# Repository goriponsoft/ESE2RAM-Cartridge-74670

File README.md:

# 似非²RAMカートリッジ(1Mbyte版)
[English README is here](README-en.md)

これは、汎用ロジックICによりメガROMコントローラと同等の動作を実現し、それを利用して似非RAMを構築したMSX用カートリッジ(命名:似非・似非RAMまたは似非²RAM)です。
ごりぽんハードウェア(同人サークル・ごりぽんソフトウェアのハードウェア部門)により作成されました。

KiCAD7用の回路図データ・基板データ・ガーバーデータを、クリエイティブ・コモンズライセンス(CC-BY-NC)で公開しています。
[MGINST215.zip](https://github.com/goriponsoft/ESE2RAM-Cartridge-74670/blob/main/MGINST215.zip)および[KSAVER105.zip](https://github.com/goriponsoft/ESE2RAM-Cartridge-74670/blob/main/KSAVER105.zip)はCCライセンスの対象ではなく、元のライセンスと条件が適用されます。

X(旧Twitter): @goriponsoft

## 似非RAMディスク(似非RAM)とは？

[同人サークル・似非職人工房](http://www.hat.hi-ho.ne.jp/tujikawa/ese/)のつじかわ氏が考案した、ストレージなどとして使えるMSX用の汎用バックアップRAMカートリッジです。

通常は、ゲームのメガROMカートリッジを改造し、ROMをRAMに置き換えることで制作します。MGINSTコマンドによりDOSカーネルをインストールしてSSDのようなストレージとして利用したり(似非RAMディスク)、メガROMのイメージを読み込ませて動作させたりすることができます。

もともとストレージとしての使用を前提に考案されたため、カートリッジ自体も「似非RAMディスク」と呼ぶほうが一般的です。

なお、所有していないゲームのイメージを読み込ませて利用することは違法行為です。通常は似非RAMディスクの他、似非RAMに改造することで使用できなくなる改造元ゲームカートリッジのイメージ(改造前にファイルに書き出しておく必要あり)、フリーウェア、自作ROMゲーム、などを動作させるのに使用します。

似非RAMディスクについての詳細は、[似非職人工房の似非RAMディスクのページ](http://www.hat.hi-ho.ne.jp/tujikawa/ese/eseram.html)を参照してください。

## 似非²RAM(似非・似非RAM)とは？

近年MSXゲームの入手自体が難しくなり、貴重になってしまったメガROMカートリッジを潰して似非RAMにするのはかなり躊躇われる状況でした。そこで、普通に入手できる汎用ロジックICを使い、メガROMコントローラーと同等の回路を実現し、それを利用して似非RAMとして組み上げたのがこのカートリッジです。

似非RAMでありながら、メガROMコントローラを使用していない「似て非なる似非RAM」ということで「似非・似非RAM」、転じて「似非の2乗」で「似非²RAM」と命名しました。上付き文字の使用に問題がある場合は「似非2RAM」や「似非似非RAM」でも構いません。英語表記は「ESE-ESE-RAM」または「ESE2-RAM」です。

## 部品表
注意: 基板Rev.6以降U3～U5が74HCシリーズから74AHCシリーズに変更されています
|部品番号|内容|数量|
|:--|:--|--:|
|BT1|CR2032電池ホルダ "CH29-2032LF"/"CH28-2032LF(TR)"/"CH004-2032LF"/"CH004-2032LF"のいずれか|1|
|C1-C8|セラミックコンデンサ 0.1μF・50V・2.5mmピッチ|8|
|C9|電解コンデンサ 47μF・16V|1|
|D1-D2|ダイオード "1N4148"|2|
|IC1-IC2|4Mbit SRAM(628512タイプ・512K×8) DIP-32 "AS6C4008"など|2|
|R1-R4|抵抗 1/4W・10KΩ|4|
|RN1|集合抵抗 8素子・10KΩ SIP-9|1|
|S1|6×6mm タクトスイッチ "TVDP01-095BB1"|1|
|U1-U2|汎用ロジックIC "74HC670"|2|
|U3|汎用ロジックIC "74AHC138"|1|
|U4|汎用ロジックIC "74AHC00"|1|
|U5|汎用ロジックIC "74AHC32"|1|
|-|CR2032電池|1|

## 組み立て方
基板の実装面積の関係で、抵抗、コンデンサ、ダイオードなどの部品が裏面(ハンダ面)に配置されているため、組み立てには注意が必要です。

[詳細な組み立てマニュアル(日本語版)はこちら](assemble_manual/main.md)

1. 基板を裏返して(コネクタの傍に「Front」と書かれている側が表面です)、シルク印刷を参考に、ダイオード、抵抗、セラミックコンデンサ、集合抵抗、の順で部品を配置して表側(部品面)からハンダ付けします。ハンダを盛りすぎると、ICと基板の間に隙間ができるので、ハンダの量は控えめにしてハンダ付けしてください。
2. ハンダ付けしたら、表面に余ったリードを切断します。リードが余分に残っていると、やはりICと基板の間に隙間ができるので、こちらもできるだけ短くなるように切断してください。
3. 基板を表に戻し、IC、電解コンデンサ、セラミックコンデンサを配置し、通常通り裏面(ハンダ面)からハンダ付けしていきます。電解コンデンサはシルク印刷の方向に横倒しにして実装してください(縦に実装するとカートリッジシェルに収まりません)。ICやコンデンサのリードの処理は通常通りで構いません。
4. タクトスイッチと電池ホルダをハンダ付けします。標準では、タクトスイッチは裏面、電池ホルダは表面に配置しますが、逆の面に配置することもできますので、お好みで配置してください。
5. ショートや部品の付け間違いがないことを念入りに確認したうえで、MSX実機に挿して動作を確認します。似非RAMディスクとして使わない場合でも、動作確認にはMGINSTを使うのが簡単です。

## 準備 (似非RAMディスクとして使う場合)
1. 似非インストーラー(MGINST.COM)とカーネルセーバー(KSAVER.COM)を入手します([似非職人工房・非公認出張所(似非なページ)](http://www.big.or.jp/~saibara/msx/ese/index-j.html)よりLHA形式のアーカイブをダウンロードすることができます。また、ZIP形式にアーカイブしなおした[MGINST215.zip](https://github.com/goriponsoft/ESE2RAM-Cartridge-74670/blob/main/MGINST215.zip)と[KSAVER105.zip](https://github.com/goriponsoft/ESE2RAM-Cartridge-74670/blob/main/KSAVER105.zip)も、こちらで用意してあります。)
2. 何らかのMSXで起動可能なストレージ(通常はフロッピーディスク)に上記ツールを展開したものと、MSX-DOSのシステムファイル(MSXDOS.SYS/COMMAND.COM)をコピーします。MSX-DOS2カーネル利用の場合は、加えてMSX-DOS2のシステムファイル(MSXDOS2.SYS/COMMAND2.COM)をコピーしておくと、似非RAMインストール時に自動的にコピーされ、MSX-DOS2で起動することができるようになります。
3. MSX実機に似非²RAMカートリッジを挿し、タクトスイッチを押したまま電源を入れ、手順2で作成したストレージからMSX-DOS(またはMSX-DOS2)を起動します。
4. KSAVER.COMを使用し、MSX本体からMSX-DOSまたはMSX-DOS2のカーネルをファイルに保存します(詳細はKSAVERの付属ドキュメントを参照)。
5. MGINST.COMを使用し、手順4で保存したカーネルのファイルを指定して似非RAMカーネルをインストールします(詳細はMGINSTの付属ドキュメントを参照)。
6. リセットし似非RAMディスクから起動することを確認します。

手順4で保存したカーネルファイルは不要ですので、削除してしまっても構いません。残しておくと、似非RAMディスクの再インストール時に手順を省略できます。

手順5でエラーが出る場合は、部品のハンダ付け不良の可能性が高いので、基板をチェックしてみてください。

## 使い方 (メガROMソフトウェアを動かす場合)
使用した部品の機能の関係で、当カートリッジでは、セグメント番号の初期値がASCIIマッパーと異なっているため、プログラムによるレジスタの初期化が必須となっています。似非RAMディスクやゲームを含む、ほとんどのメガROMソフトウェアでは適切に初期化が行われているので問題ありませんが、初期化を怠っていたり、セグメント初期値が特定の値であることを期待しているソフトウェアは動作しない場合があります。

当カートリッジの起動直後もしくはリセット直後のバンクは以下のようになっています。

|バンクアドレス|レジスタアドレス|セグメント番号|
|:--|:--|--:|
|4000h-5FFFh|6000h-67FFh|0|
|6000h-7FFFh|6800h-6FFFh|0|
|8000h-9FFFh|7000h-77FFh|0|
|A000h-BFFFh|7800h-7FFFh|0|

この状態からレジスタに値を書き込むと、書き込んだレジスタは書き込んだ値に、書き込まれていないレジスタは不定値に切り替わります。

例えば6000hに0を書き込んだ場合は以下のようになります。

|バンクアドレス|セグメント番号|
|:--|--:|
|4000h-5FFFh|0|
|6000h-7FFFh|不定|
|8000h-9FFFh|不定|
|A000h-BFFFh|不定|

このため、当カートリッジで自作メガROMソフトウェアを動作させる場合は、INITエントリのできるだけ早い段階で、実行中のアドレスを含むバンクのレジスタに0を書き込んで初期化する必要があります。実行中のアドレスを含まないバンクのレジスタに先に書き込んでしまうと、実行中のプログラムが不定のバンクに切り替わり、ほとんどの場合は暴走します。また、書き込まれなかったレジスタの値は不定ですので、必要であれば初期化を行ってください。

通常はセグメント#0に以下のコードを配置し、ROMヘッダのINITエントリより4000h～5FFFhバンクのコードとして呼び出せば、問題なく初期化できます。
```
	xor		a
	ld		(6000h),a
	ld		(6800h),a
	ld		(7000h),a
	ld		(7800h),a
```

## 互換性情報
動作確認済のハードウェア(順不同)について

ご報告いただいたものは順次追加していきます

### 動作不良が確認されている機種と症状

- ビクター HC-90 および HC-95 (MSX2) : RAMから読み出されたデータが壊れるため正常動作しない
- 東芝 HX-E601 (拡張スロット) : 認識されず起動しない

### 正常動作が確認されている機種

- パナソニック FS-A1ST
- ソニー HB-F1XV
- 三菱 ML-G30model1 および ML-G30model2
- ヤマハ YIS503 および CX5F
- ヤマハ YIS604/128 および CX7M/128
- 三洋 WAVY70FD および WAVY70FD2
- 東芝 HX-31
- 三菱 ML-8000
- ゼネラル PCT-50 および PCT-55
- ソニー HB-F500

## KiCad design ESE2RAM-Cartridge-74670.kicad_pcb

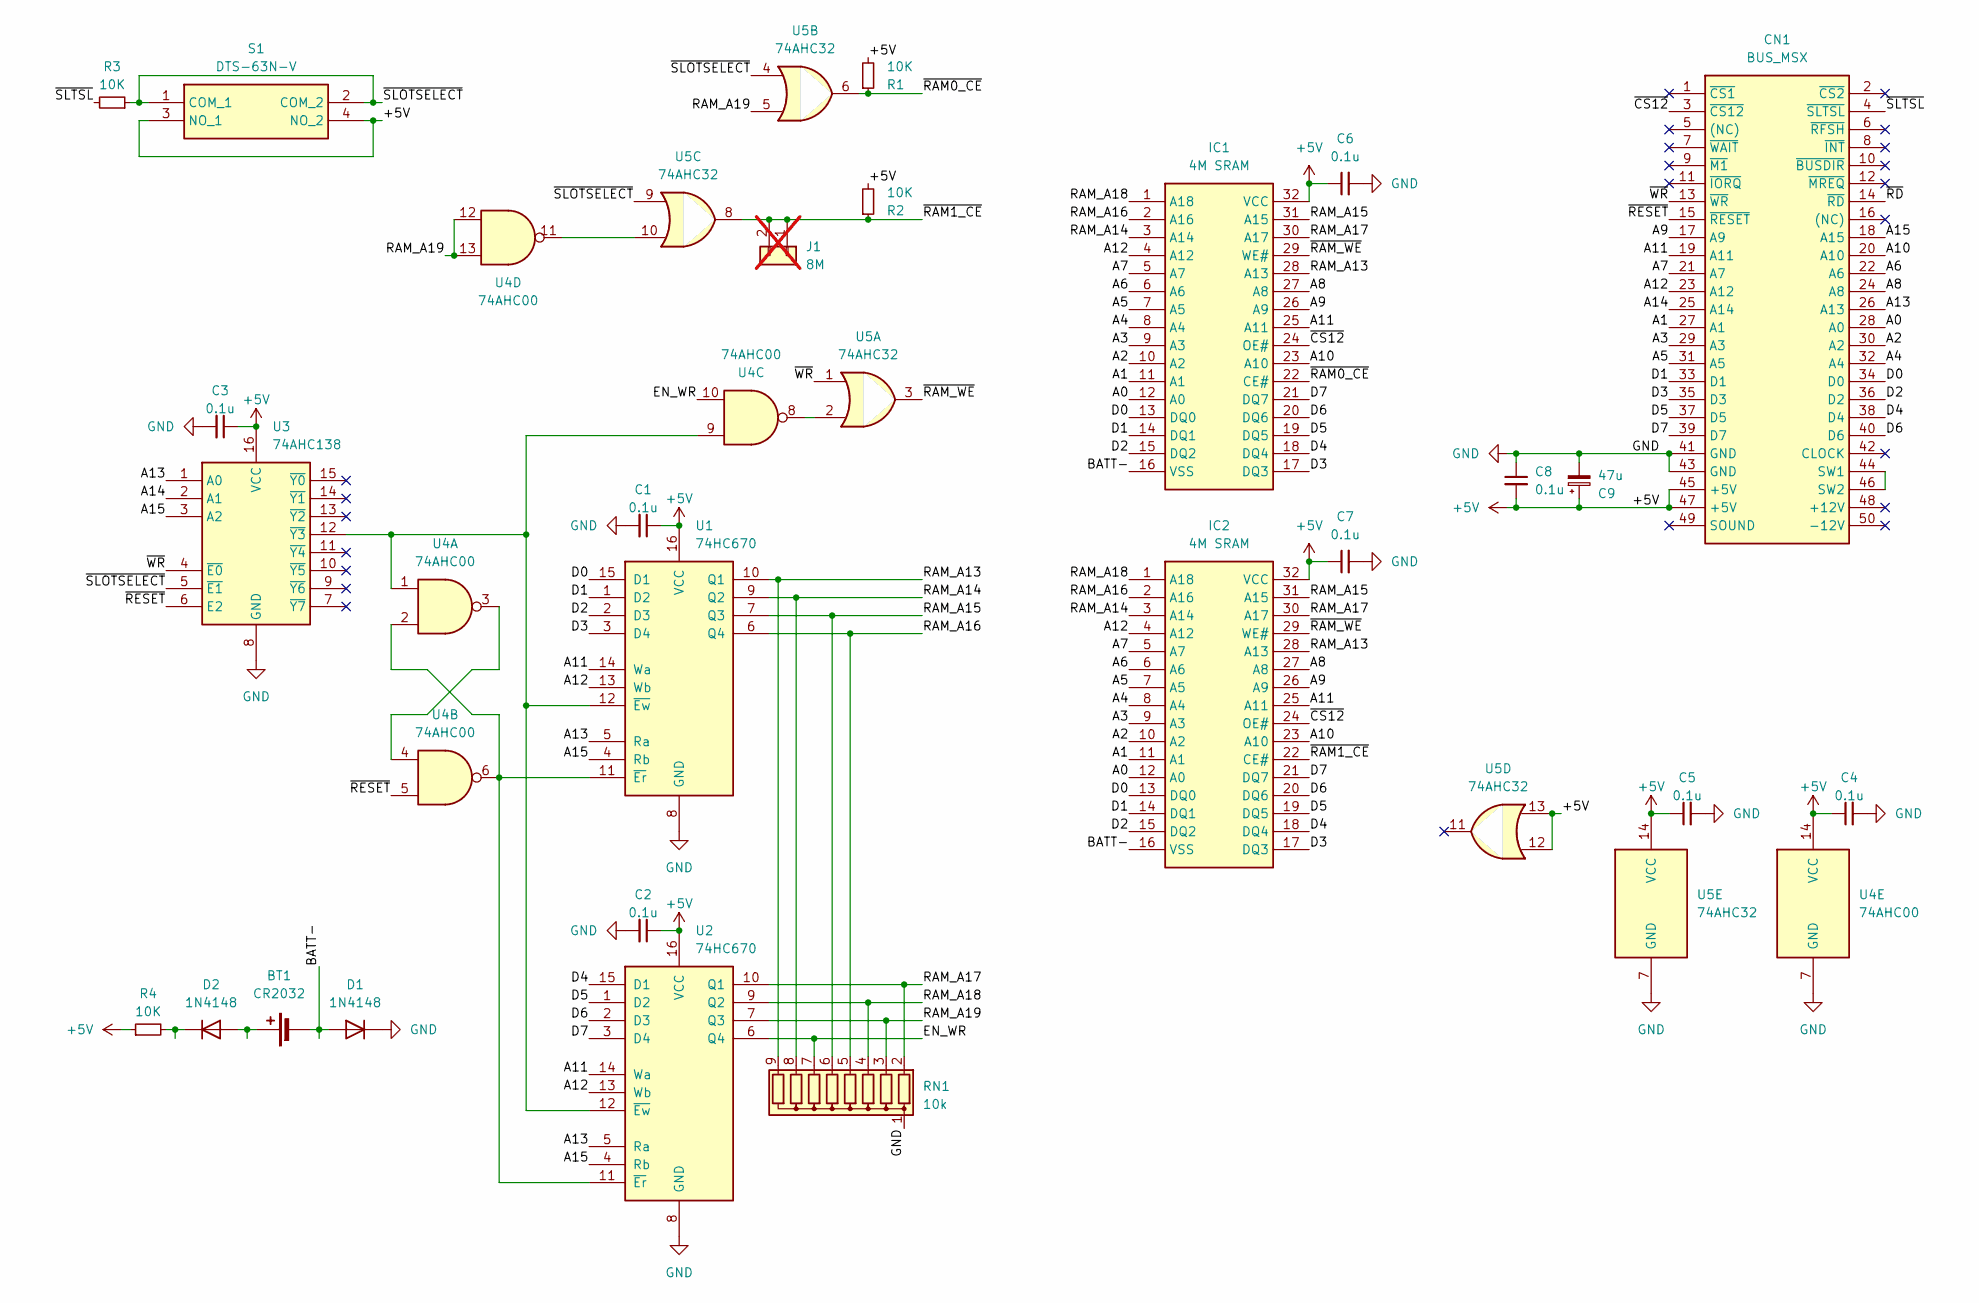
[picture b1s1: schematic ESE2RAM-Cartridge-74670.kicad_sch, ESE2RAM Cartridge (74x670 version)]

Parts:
BT1: CR2032; BatteryHolder_CH2x-2032LF
C1, C2, C3, C4, C5, C6, C7, C8: 0.1u; C_Disc_D3.0mm_W1.6mm_P2.50mm
C9: 47u; CP_Radial_D5.0mm_P2.00mm_Horizontal
CN1: BUS_MSX; BUS_MSX_CARD_SHORT
D1, D2: 1N4148; D_DO-35_SOD27_P7.62mm_Horizontal
IC1, IC2: 4M SRAM; DIP32_600mil_FineLongPad; Manufacturer_Part_Number AS6C4008-55PIN; Mouser Part Number 913-AS6C4008-55PIN
J1: 8M; PinHeader_1x02_P2.00mm_Vertical; not fitted
R1, R2, R3, R4: 10K; R_Axial_DIN0207_L6.3mm_D2.5mm_P7.62mm_Horizontal
RN1: 10k; R_Array_SIP9
S1: DTS-63N-V; DTS63NV; Manufacturer_Part_Number DTS-63N-V; Mouser Part Number 113-DTS-63N-V
U1, U2: 74HC670; DIP16_300mil_FineLongPad
U3: 74AHC138; DIP16_300mil_FineLongPad
U4: 74AHC00; DIP14_300mil_FineLongPad
U5: 74AHC32; DIP14_300mil_FineLongPad

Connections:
+5V: C1.1, C2.1, C3.1, C4.1, C5.1, C6.1, C7.1, C8.2, C9.1, CN1.45 (+5V), CN1.47 (+5V), IC1.32 (VCC), IC2.32 (VCC), R1.2, R2.2, R4.1, S1.3 (NO_1), S1.4 (NO_2), U1.16 (VCC), U2.16 (VCC), U3.16 (VCC), U4.14 (VCC), U5.12, U5.13, U5.14 (VCC)
/A0: CN1.28 (A0), IC1.12 (A0), IC2.12 (A0)
/A1: CN1.27 (A1), IC1.11 (A1), IC2.11 (A1)
/A2: CN1.30 (A2), IC1.10 (A2), IC2.10 (A2)
/A3: CN1.29 (A3), IC1.9 (A3), IC2.9 (A3)
/A4: CN1.32 (A4), IC1.8 (A4), IC2.8 (A4)
/A5: CN1.31 (A5), IC1.7 (A5), IC2.7 (A5)
/A6: CN1.22 (A6), IC1.6 (A6), IC2.6 (A6)
/A7: CN1.21 (A7), IC1.5 (A7), IC2.5 (A7)
/A8: CN1.24 (A8), IC1.27 (A8), IC2.27 (A8)
/A9: CN1.17 (A9), IC1.26 (A9), IC2.26 (A9)
/A10: CN1.20 (A10), IC1.23 (A10), IC2.23 (A10)
/A11: CN1.19 (A11), IC1.25 (A11), IC2.25 (A11), U1.14 (Wa), U2.14 (Wa)
/A12: CN1.23 (A12), IC1.4 (A12), IC2.4 (A12), U1.13 (Wb), U2.13 (Wb)
/A13: CN1.26 (A13), U1.5 (Ra), U2.5 (Ra), U3.1 (A0)
/A14: CN1.25 (A14), U3.2 (A1)
/A15: CN1.18 (A15), U1.4 (Rb), U2.4 (Rb), U3.3 (A2)
/BATT-: BT1.2 (-), D1.2 (A), IC1.16 (VSS), IC2.16 (VSS)
/D0: CN1.34 (D0), IC1.13 (DQ0), IC2.13 (DQ0), U1.15 (D1)
/D1: CN1.33 (D1), IC1.14 (DQ1), IC2.14 (DQ1), U1.1 (D2)
/D2: CN1.36 (D2), IC1.15 (DQ2), IC2.15 (DQ2), U1.2 (D3)
/D3: CN1.35 (D3), IC1.17 (DQ3), IC2.17 (DQ3), U1.3 (D4)
/D4: CN1.38 (D4), IC1.18 (DQ4), IC2.18 (DQ4), U2.15 (D1)
/D5: CN1.37 (D5), IC1.19 (DQ5), IC2.19 (DQ5), U2.1 (D2)
/D6: CN1.40 (D6), IC1.20 (DQ6), IC2.20 (DQ6), U2.2 (D3)
/D7: CN1.39 (D7), IC1.21 (DQ7), IC2.21 (DQ7), U2.3 (D4)
/EN_WR: RN1.7 (R6), U2.6 (Q4), U4.10
/RAM_A13: IC1.28 (A13), IC2.28 (A13), RN1.9 (R8), U1.10 (Q1)
/RAM_A14: IC1.3 (A14), IC2.3 (A14), RN1.8 (R7), U1.9 (Q2)
/RAM_A15: IC1.31 (A15), IC2.31 (A15), RN1.6 (R5), U1.7 (Q3)
/RAM_A16: IC1.2 (A16), IC2.2 (A16), RN1.5 (R4), U1.6 (Q4)
/RAM_A17: IC1.30 (A17), IC2.30 (A17), RN1.2 (R1), U2.10 (Q1)
/RAM_A18: IC1.1 (A18), IC2.1 (A18), RN1.4 (R3), U2.9 (Q2)
/RAM_A19: RN1.3 (R2), U2.7 (Q3), U4.12, U4.13, U5.5
/~CS12: CN1.3 (~CS12), IC1.24 (OE#), IC2.24 (OE#)
/~RAM0_CE: IC1.22 (CE#), R1.1, U5.6
/~RAM1_CE: IC2.22 (CE#), J1.1, J1.2, R2.1, U5.8
/~RAM_WE: IC1.29 (WE#), IC2.29 (WE#), U5.3
/~RD: CN1.14 (~RD)
/~RESET: CN1.15 (~RESET), U3.6 (E2), U4.5
/~SLOTSELECT: R3.1, S1.1 (COM_1), S1.2 (COM_2), U3.5 (~E1), U5.4, U5.9
/~SLTSL: CN1.4 (~SLTSL), R3.2
/~WR: CN1.13 (~WR), U3.4 (~E0), U5.1
GND: C1.2, C2.2, C3.2, C4.2, C5.2, C6.2, C7.2, C8.1, C9.2, CN1.41 (GND), CN1.43 (GND), D1.1 (K), RN1.1 (common), U1.8 (GND), U2.8 (GND), U3.8 (GND), U4.7 (GND), U5.7 (GND)
unnamed: BT1.1 (+), D2.2 (A)
unnamed: CN1.44 (SW1), CN1.46 (SW2)
unnamed: D2.1 (K), R4.2
unnamed: U1.11 (~Er), U2.11 (~Er), U4.2, U4.6
unnamed: U1.12 (~Ew), U2.12 (~Ew), U3.12 (~Y3), U4.1, U4.9
unnamed: U4.3, U4.4
unnamed: U4.8, U5.2
unnamed: U4.11, U5.10

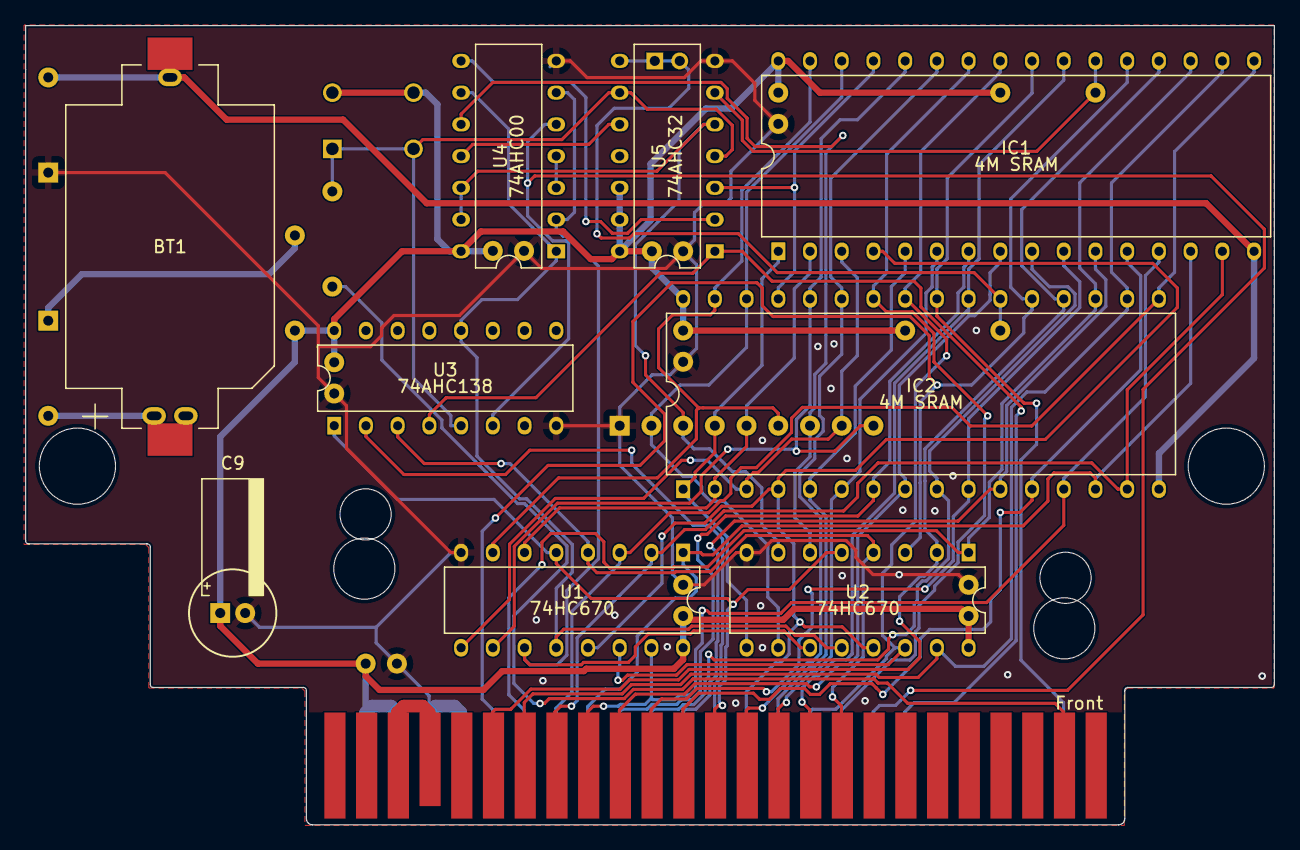
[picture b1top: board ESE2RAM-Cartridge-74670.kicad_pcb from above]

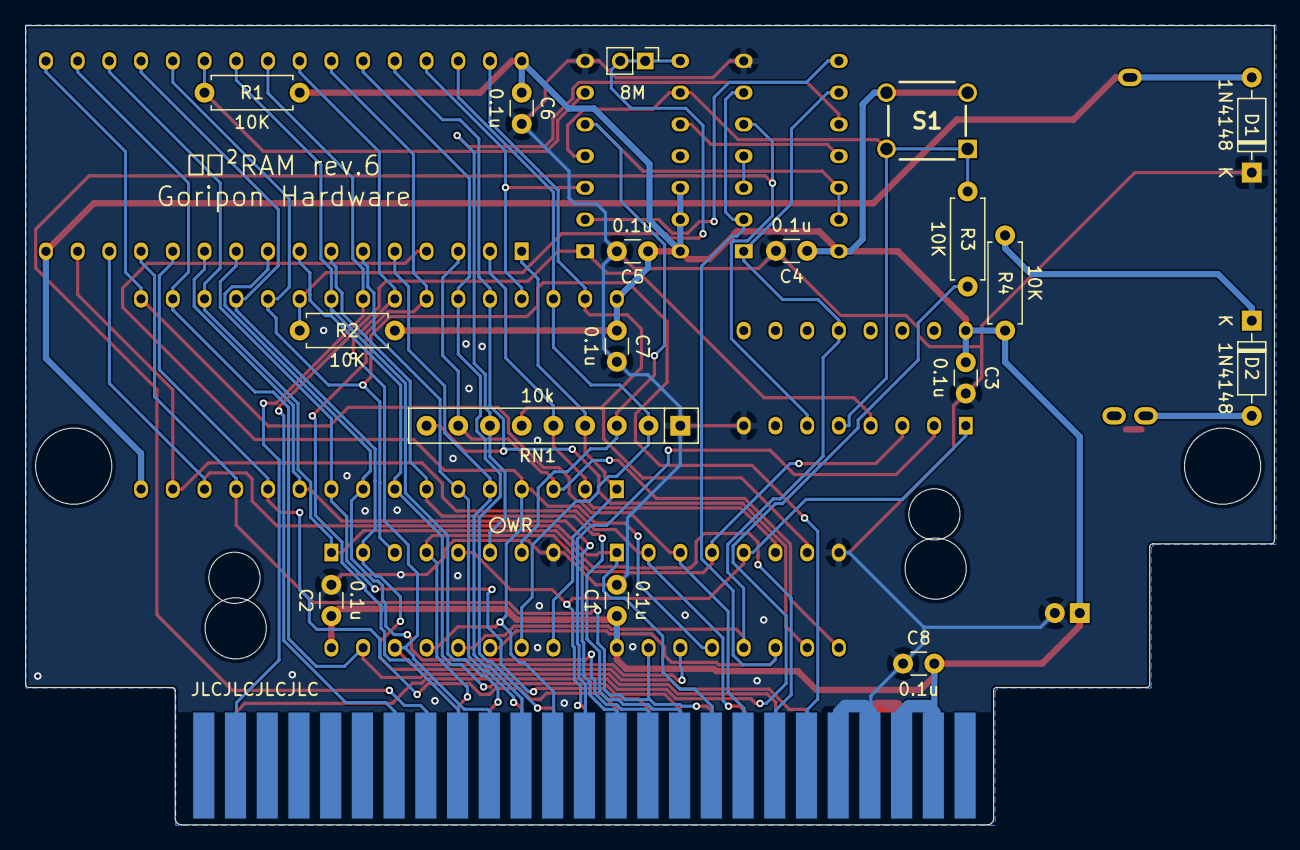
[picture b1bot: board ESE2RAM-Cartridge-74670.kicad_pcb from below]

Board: 2 copper layers, 100.0 x 64.0 mm, 27 parts (17 on the bottom side), 51 nets.

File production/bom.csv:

Designator,Footprint,Quantity,Value,LCSC Part #
BT1,BatteryHolder_CH2x-2032LF,1,CR2032,
"C1, C2, C3, C4, C5, C6, C7, C8",C_Disc_D3.0mm_W1.6mm_P2.50mm,8,0.1u,
C9,CP_Radial_D5.0mm_P2.00mm_Horizontal,1,47u,
"D1, D2",D_DO-35_SOD27_P7.62mm_Horizontal,2,1N4148,
"IC1, IC2",DIP32_600mil_FineLongPad,2,4M SRAM,
"R1, R2, R3, R4",R_Axial_DIN0207_L6.3mm_D2.5mm_P7.62mm_Horizontal,4,10K,
RN1,R_Array_SIP9,1,10k,
S1,DTS63NV,1,DTS-63N-V,
"U1, U2",DIP16_300mil_FineLongPad,2,74HC670,
U3,DIP16_300mil_FineLongPad,1,74AHC138,
U4,DIP14_300mil_FineLongPad,1,74AHC00,
U5,DIP14_300mil_FineLongPad,1,74AHC32,

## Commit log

2024-03-24 First Release
2024-03-25 Modified README
    Modified README
    Added "How to assemble" item.
2024-03-25 Modified schematic
    Modified schematic
    Change tactile switch.
2024-03-25 Modified README
    Modified README
    Corrected "Preparation" item.
2024-03-25 Modified Schematic
    Modified Schematic
    Fixed DRC error in PCB data & Rebuilt Gerber data.
2024-03-27 Modified README
    公開しているデータについての説明を追加。
    Added explanation about published data.
2024-03-28 Modified README
    部品表のセラミックコンデンサにリード間隔を追加、組み立て方に動作確認の手順を追加、ほか細かい文言の修正。
    Added lead spacing to ceramic capacitors in the parts list, added operation confirmation steps to assembly instructions, and other minor wording corrections.
2024-03-31 Added tools archive.
    ツール類のzipアーカイブを追加。
    Added tool zip archive.
2024-03-31 Modified README
    KSAVER105.zipのライセンスに関する項目が抜けていたので追加。
    Added the item related to the license of KSAVER105.zip because it was missing.
2024-04-04 Modify Schematic
    プロジェクトローカルライブラリの設定が抜けていたのを修正。
    Fixed missing project local library settings.
    その他の細かな修正。
    Other minor corrections.
2024-04-12 Modified Schematic
    電解コンデンサの容量を10μFから47μFに変更
    電池ソケットのシルク印刷の切り欠き位置が間違っていたのを修正
    不要なファイルの削除
    その他細かな修正
    Changed the capacitance of electrolytic capacitor from 10uF to 47uF.
    Fixed an issue where the notch position on the silkscreen print on the battery socket was incorrect.
2024-04-12 Modified README
    READMEの部品表を回路図に合わせて修正
    その他細かな文言の修正
    Modified the README parts list to match the schematic.
    Other minor wording corrections.
2024-04-13 Modified Schematic
    部品の配置およびフットプリントの修正と、ガーバーデータへの反映
    Modify part placement and footprint and reflect in Gerber data.
2024-04-13 Modified README
    修正した回路図に合わせて組み立て方を修正
    Modified "How to assemble" according to the revised schematic.
2024-04-13 Modified Schematic
    カードエッジコネクタのパッド形状(SW2/+12V/-12V)を修正
    Corrected the pad shape (SW2/+12V/-12V) of the card edge connector.
2024-04-14 Modified Schematic, and README
    電解コンデンサのフットプリントを修正
    組み立て方に電解コンデンサの実装方法を追記
    Fixed electrolytic capacitor footprint.
    Added the mounting method of electrolytic capacitor to "How to assemble".
2024-06-08 Updated Schematic & Gerber data.
    Updated to revision 4.
2024-07-23 Modified README
    「使い方(メガROMソフトウェアを動かす場合)」の項目にセグメント(バンク番号)の初期化について記載
    Initialization of segments (bank numbers) is described in the "How to use (when running Mega ROM software)" section.
2024-10-08 Modified README
    Corrected wording in README
    READMEの文言ほか修正
2024-10-08 Modified Pictures
    基板写真のリンクと画像データを修正
    Corrected the board photo link and image data.
2024-10-08 Updated Schematic & Gerber data
    回路図データとガーバーデータを更新
    Updated Schematic & Gerber data.
2025-02-10 Add assemble_manual
    Add Japanese assemble manual
2025-02-10 Modified README
    バンク初期値の記述の修正。
    Correction of bank initial value description.
2025-03-11 Add Assembly manulal & ese2boot command
    日本語版組み立てマニュアルを追加
    Added Japanese assembly manual
    バンク初期化を行いブートする補助コマンドESE2BOOT.COMを追加
    Added auxiliary command ESE2BOOT.COM to initialize banks and boot.
2025-03-11 Assembly Manual & README modified
    組み立てマニュアルの画像挿し替えと細かな文言の修正
    The images in the assembly manual have been replaced and minor wording has been corrected.
    READMEの「使い方」の項目に初期化コードの例を追加
    Added example initialization code to the "How to use" section of the README.
2025-03-12 Update README.md
    セグメント番号初期値の表を修正
    Corrected the table of segment number initial values.
2025-03-23 PCB modified
    PCBを修正
    PCB modified.
    U4, U5, IC1の位置を下にずらした
    U4, U5, and IC1 shifted downward.
    その他細かな修正
    Other minor modifications.
2025-04-06 Modified Schematic
    一部MSX機種での動作不良修正のため74HC00/74HC32/74HC138を74AHCシリーズに変更
    Changed 74HC00/74HC32/74HC138 to 74AHC series to fix malfunction on some MSX models.
2025-04-06 Modified README
    回路図に合わせてREADMEに記載の部品表を修正
    The parts list in the README has been updated to match the schematic.
2025-04-06 Modified PCB
    基板上のシルク印刷のバージョン番号を修正
    Corrected version number on PCB silkscreen.
2025-04-11 Modified ESE2BOOT.COM & Schematic
    ESE2BOOT.COMのバグ修正
    Fixed a bug in ESE2BOOT.COM
    回路図データの微修正
    Minor corrections to schematic data.
2025-04-12 Modified README
    READMEの部品表に部品変更の注意書きを足した
    Added a note about part changes to the README parts list.
2025-04-13 Modified schematic data
    一部のシンボルをプロジェクトのライブラリにコピーし、それに合わせ回路図を修正した
    I copied some symbols into the project library and modified the schematic accordingly.
2025-04-20 Modified README and assemble_manual
    READMEに互換性情報の項目を追加
    Added compatibility information section to README.
    assemble_manualにRAM容量減量の改造例を追加
    Added an example of a modification to reduce RAM capacity to the assemble_manual.
    その他の微細な修正
    Other minor fixes.
